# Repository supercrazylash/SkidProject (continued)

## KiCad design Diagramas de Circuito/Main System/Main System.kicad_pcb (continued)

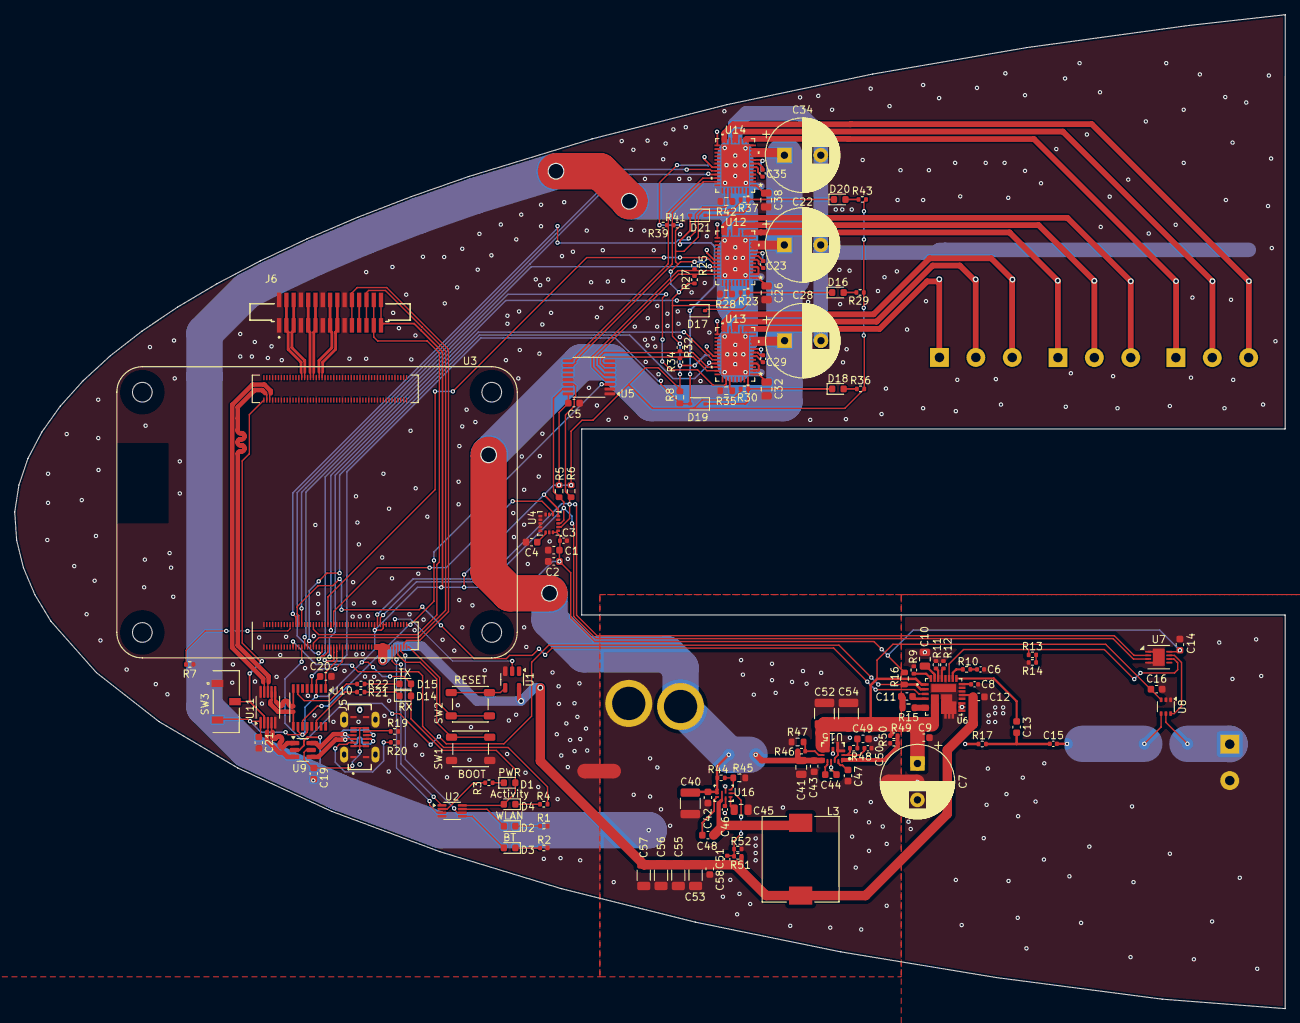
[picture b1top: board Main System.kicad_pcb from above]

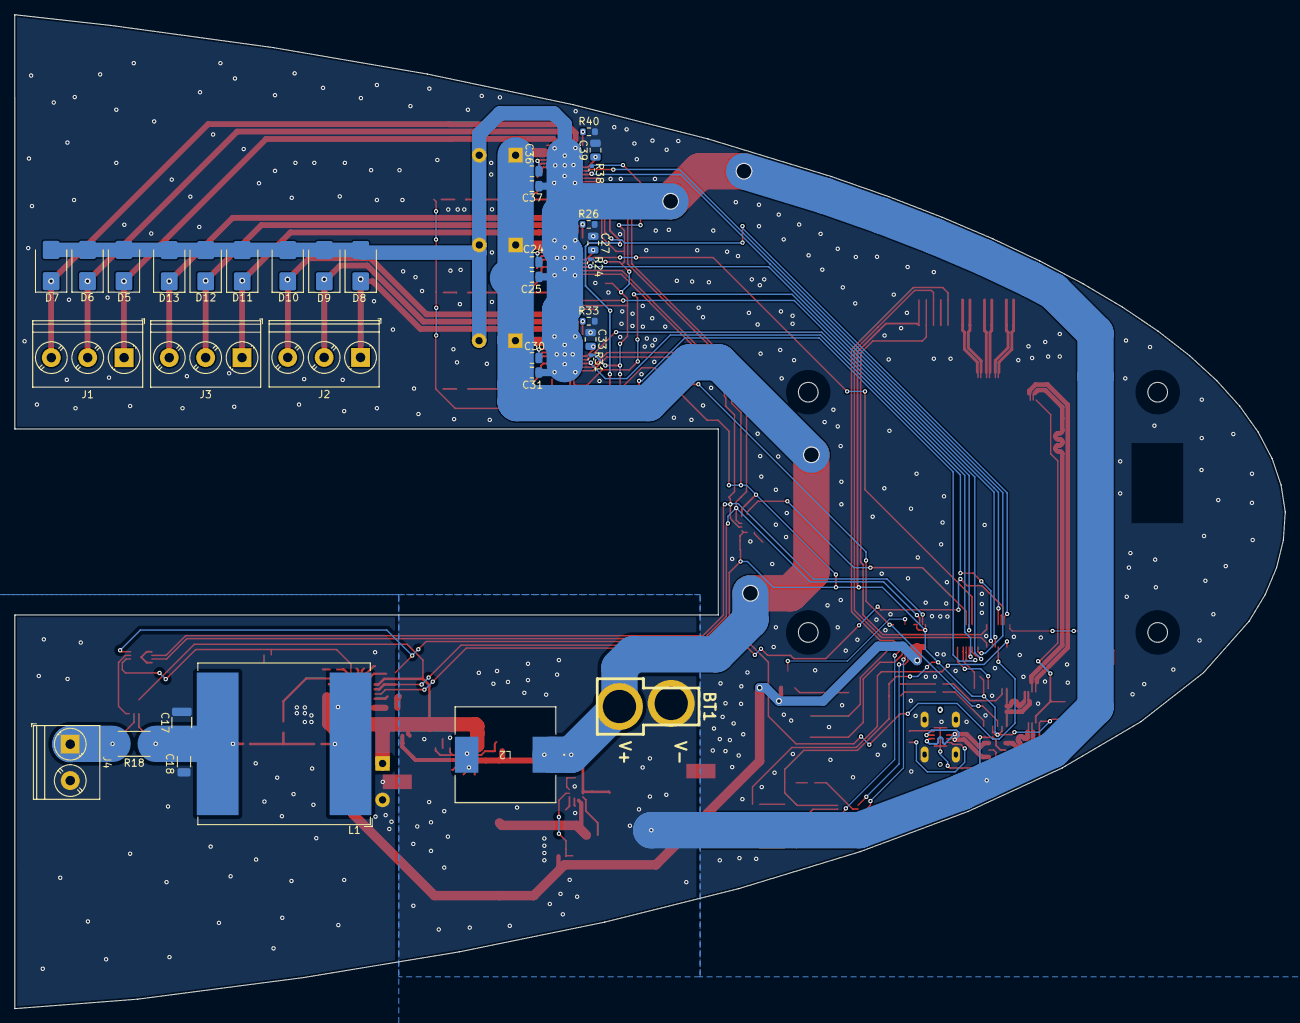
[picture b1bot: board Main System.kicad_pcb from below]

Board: 2 copper layers, 174.5 x 136.5 mm, 162 parts (34 on the bottom side), 140 nets.

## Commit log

2024-10-25 whatever
2024-10-25 Teste
    imagem
2024-10-25 testImage
2024-10-25 çouhkuygu
2024-10-25 relatorio horrivel
2024-11-09 price table start
2024-11-09 price table v2
2024-11-09 price table v3
2024-11-09 price table v4
2024-11-14 colen
2024-11-14 colen rizz
2024-11-14 capa atualizationss
2024-11-14 paulinho goat
2024-11-14 tropacolen ataca o pentagono
2024-11-14 toilet
2024-11-14 skibidi
2024-11-14 skibidi rizz
2024-11-14 sporting campeao champions
2024-11-14 paulinho bola de ouro
2024-11-21 upaa
2024-11-21 paulinhogoat
2024-11-21 dababy
2024-11-21 dadasdasdasd
2024-11-21 dfsdfsdfyuhuhsdfasdk
2024-11-21 sdhiasdsjhlasdf
2024-11-21 asduasdasdjhkasdhkasd
2024-11-21 paulinhoo
2024-11-21 aulinho
2024-11-21 asasdasd
2024-11-21 sdsdfsdfhsdfuisdf
2024-11-21 dfdfsdfsasdf
2024-11-21 iasdfisdhsdfajhasdd
2024-11-21 pick up the phonee
2024-11-21 sdfasdafsdfeeeww
2024-11-22 report start
2024-11-22 mais relatorio
2025-01-26 idefk
2025-02-24 circuit
2025-02-24 added .DS_Store to gitignore
2025-02-24 gitignore fixes
